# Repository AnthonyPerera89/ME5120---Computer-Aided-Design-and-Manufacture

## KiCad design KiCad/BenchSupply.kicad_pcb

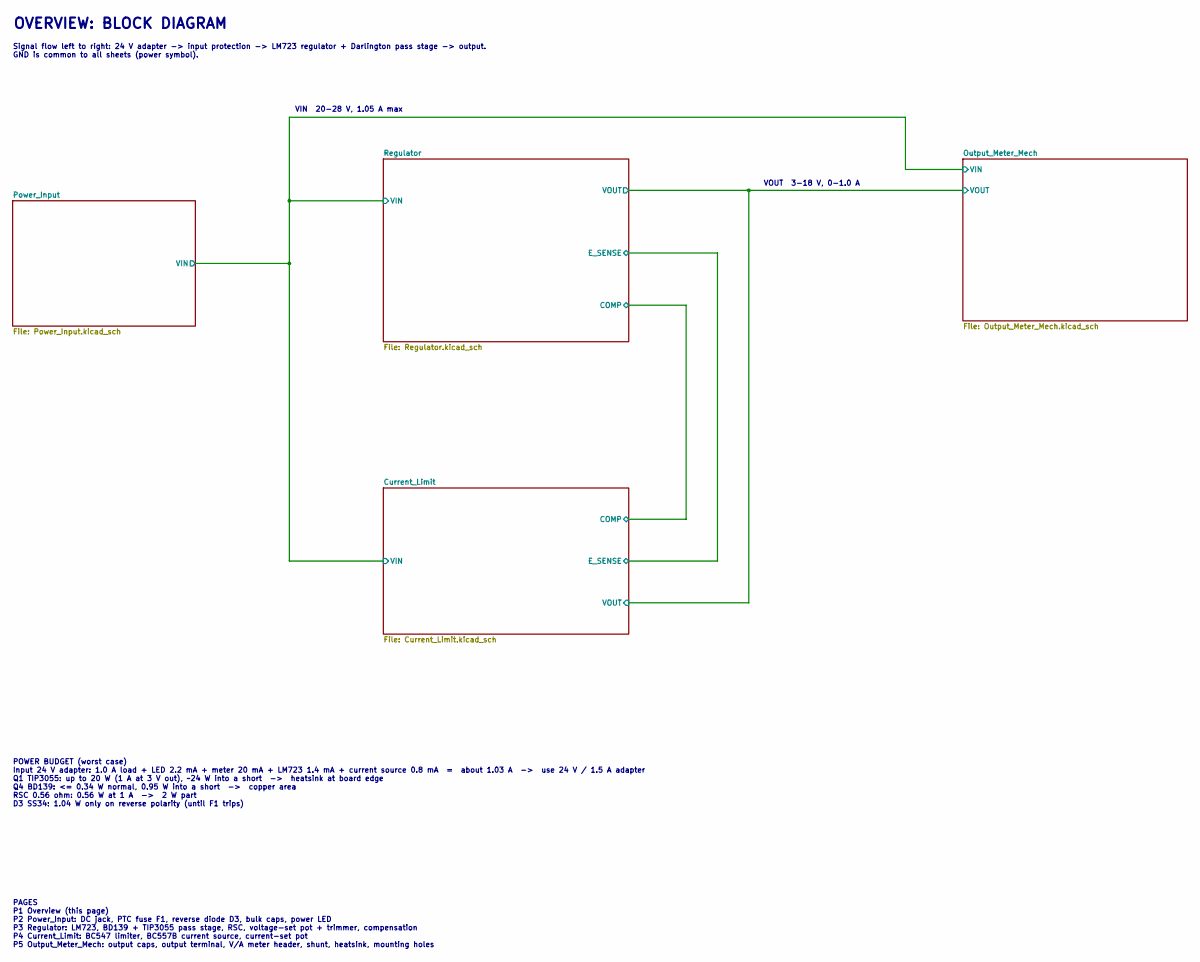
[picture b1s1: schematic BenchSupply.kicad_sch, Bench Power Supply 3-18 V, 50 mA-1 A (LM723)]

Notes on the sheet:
PAGES P1 Overview (this page) P2 Power_Input: DC jack, PTC fuse F1, reverse diode D3, bulk caps, power LED P3 Regulator: LM723, BD139 + TIP3055 pass stage, RSC, voltage-set pot + trimmer, compensation P4 Current_Limit: BC547 limiter, BC557B current source, current-set pot P5 Output_Meter_Mech: outp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
Signal flow left to right: 24 V adapter -> input protection -> LM723 regulator + Darlington pass stage -> output. GND is common to all sheets (power symbol).
VIN 20-28 V, 1.05 A max
OVERVIEW: BLOCK DIAGRAM
POWER BUDGET (worst case) Input 24 V adapter: 1.0 A load + LED 2.2 mA + meter 20 mA + LM723 1.4 mA + current source 0.8 mA = about 1.03 A -> use 24 V / 1.5 A adapter Q1 TIP3055: up to 20 W (1 A at 3 V out), ~24 W into a short -> heatsink at board edge Q4 BD139: <= 0.34 W normal, 0.95 W into a short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
VOUT 3-18 V, 0-1.0 A

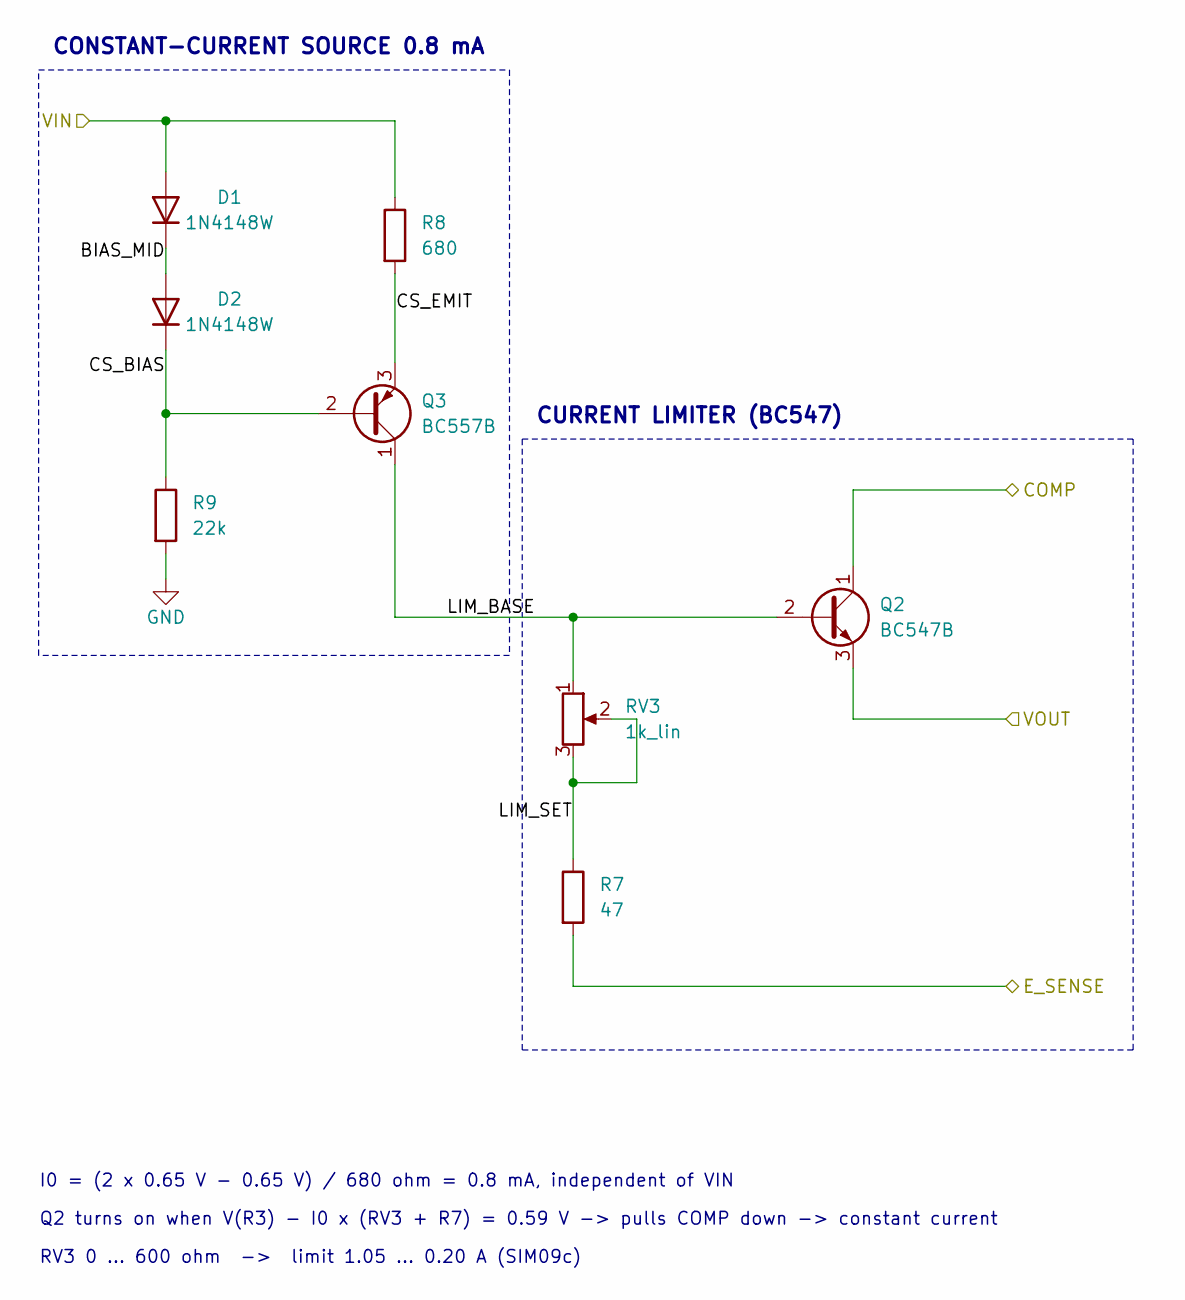
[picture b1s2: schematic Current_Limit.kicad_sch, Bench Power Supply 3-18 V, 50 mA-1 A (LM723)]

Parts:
D1, D2: 1N4148W; D_SOD-123; MPN Vishay 1N4148W
Q2: BC547B; TO-92_Inline_Wide; Rating Brief part; turns on at VBE ~0.59 V and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; MPN onsemi BC547BTA
Q3: BC557B; TO-92_Inline_Wide; Rating Constant-current source I0 = (2 VD - VE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; MPN onsemi BC557BTA
R7: 47; R_0805_2012Metric; MPN Yageo RC0805FR-0747RL
R8: 680; R_0805_2012Metric; MPN Yageo RC0805FR-07680RL
R9: 22k; R_0805_2012Metric; MPN Yageo RC0805FR-0722KL
RV3: 1k_lin; Potentiometer_Alps_RK163_Single_Horizontal; Rating PCB-mount shaft pot, linear; wired as r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; MPN Alps RK163 series 16 mm, M7 bushing, 1k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

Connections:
/Current_Limit/BIAS_MID: D1.1 (K), D2.2 (A)
/Current_Limit/COMP: Q2.1 (C); also elsewhere on the board
/Current_Limit/CS_BIAS: D2.1 (K), Q3.2 (B), R9.1
/Current_Limit/CS_EMIT: Q3.3 (E), R8.2
/Current_Limit/E_SENSE: R7.2; also elsewhere on the board
/Current_Limit/LIM_BASE: Q2.2 (B), Q3.1 (C), RV3.1
/Current_Limit/LIM_SET: R7.1, RV3.2, RV3.3
/Current_Limit/VIN: D1.2 (A), R8.1; also elsewhere on the board
/Regulator/VOUT: Q2.3 (E); also elsewhere on the board
GND: R9.2; also elsewhere on the board

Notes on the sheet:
I0 = (2 x 0.65 V - 0.65 V) / 680 ohm = 0.8 mA, independent of VIN
RV3 0 ... 600 ohm -> limit 1.05 ... 0.20 A (SIM09c)
CONSTANT-CURRENT SOURCE 0.8 mA
CURRENT LIMITER (BC547)
Q2 turns on when V(R3) - I0 x (RV3 + R7) = 0.59 V -> pulls COMP down -> constant current

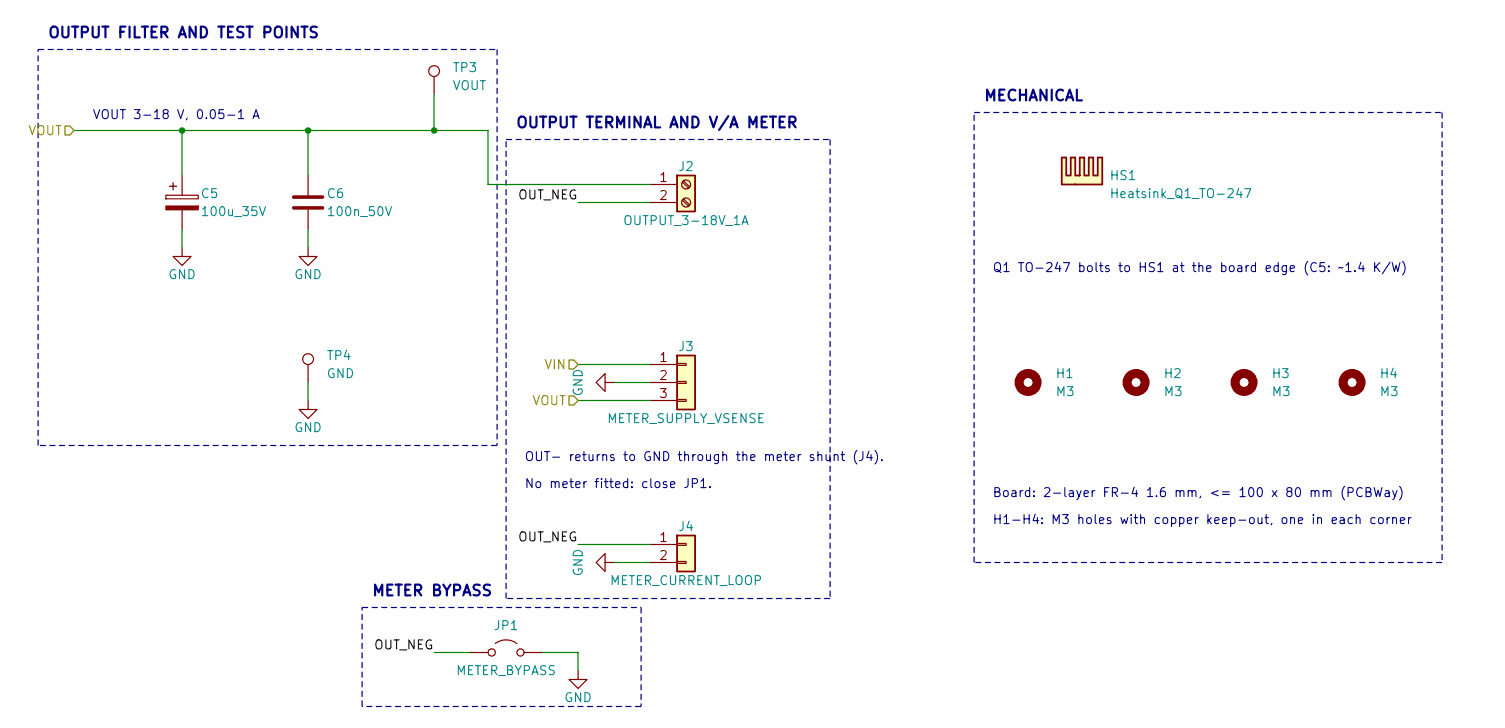
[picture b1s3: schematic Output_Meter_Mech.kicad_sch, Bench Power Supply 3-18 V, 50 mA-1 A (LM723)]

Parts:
C5: 100u_35V; CP_Radial_D6.3mm_P2.50mm; MPN Panasonic EEU-FR1V101 (100uF 35V 6.3x11)
C6: 100n_50V; C_0805_2012Metric; MPN Samsung CL21B104KBCNNNC
H1, H2, H3, H4: M3; MountingHole_3.2mm_M3
HS1: Heatsink_Q1_TO-247; Heatsink_AAVID_Extruded_531302B02500G_34.9x12.7mm_H63.5mm; Rating Board-mount TO-247 extrusion 34.9x12.7x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; MPN Aavid (Boyd) 531302B02500G
J2: OUTPUT_3-18V_1A; TerminalBlock_Phoenix_MKDS-1,5-2-5.08_1x02_P5.08mm_Horizont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; MPN Phoenix Contact 1715721 (MKDS 1,5/2-5,0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
J3: METER_SUPPLY_VSENSE; PinHeader_1x03_P2.54mm_Vertical; Rating V/A meter thin lead: 1 = VIN supply (~2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; MPN 2.54 mm male header 1x3
J4: METER_CURRENT_LOOP; TerminalBlock_Phoenix_MKDS-1,5-2-5.08_1x02_P5.08mm_Horizont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; Rating V/A meter thick leads (1 A): 1 = OUT- f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; MPN Phoenix Contact 1715721 (MKDS 1,5/2-5,0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
JP1: METER_BYPASS; PinHeader_1x02_P2.54mm_Vertical; Rating Close (solder bridge / 2-pin link) when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; MPN 2.54 mm male header 1x2 + shunt
TP3: VOUT; TestPoint_THTPad_D2.0mm_Drill1.0mm
TP4: GND; TestPoint_THTPad_D2.0mm_Drill1.0mm

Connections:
/Current_Limit/VIN: J3.1; also elsewhere on the board
/Output_Meter_Mech/OUT_NEG: J2.2, J4.1, JP1.1 (A)
/Regulator/VOUT: C5.1, C6.1, J2.1, J3.3, TP3.1 (1_1); also elsewhere on the board
GND: C5.2, C6.2, J3.2, J4.2, JP1.2 (B), TP4.1 (1_1); also elsewhere on the board

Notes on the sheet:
OUTPUT FILTER AND TEST POINTS
No meter fitted: close JP1.
Q1 TO-247 bolts to HS1 at the board edge (C5: ~1.4 K/W)
METER BYPASS
H1-H4: M3 holes with copper keep-out, one in each corner
OUTPUT TERMINAL AND V/A METER
VOUT 3-18 V, 0.05-1 A
MECHANICAL
Board: 2-layer FR-4 1.6 mm, <= 100 x 80 mm (PCBWay)
OUT- returns to GND through the meter shunt (J4).

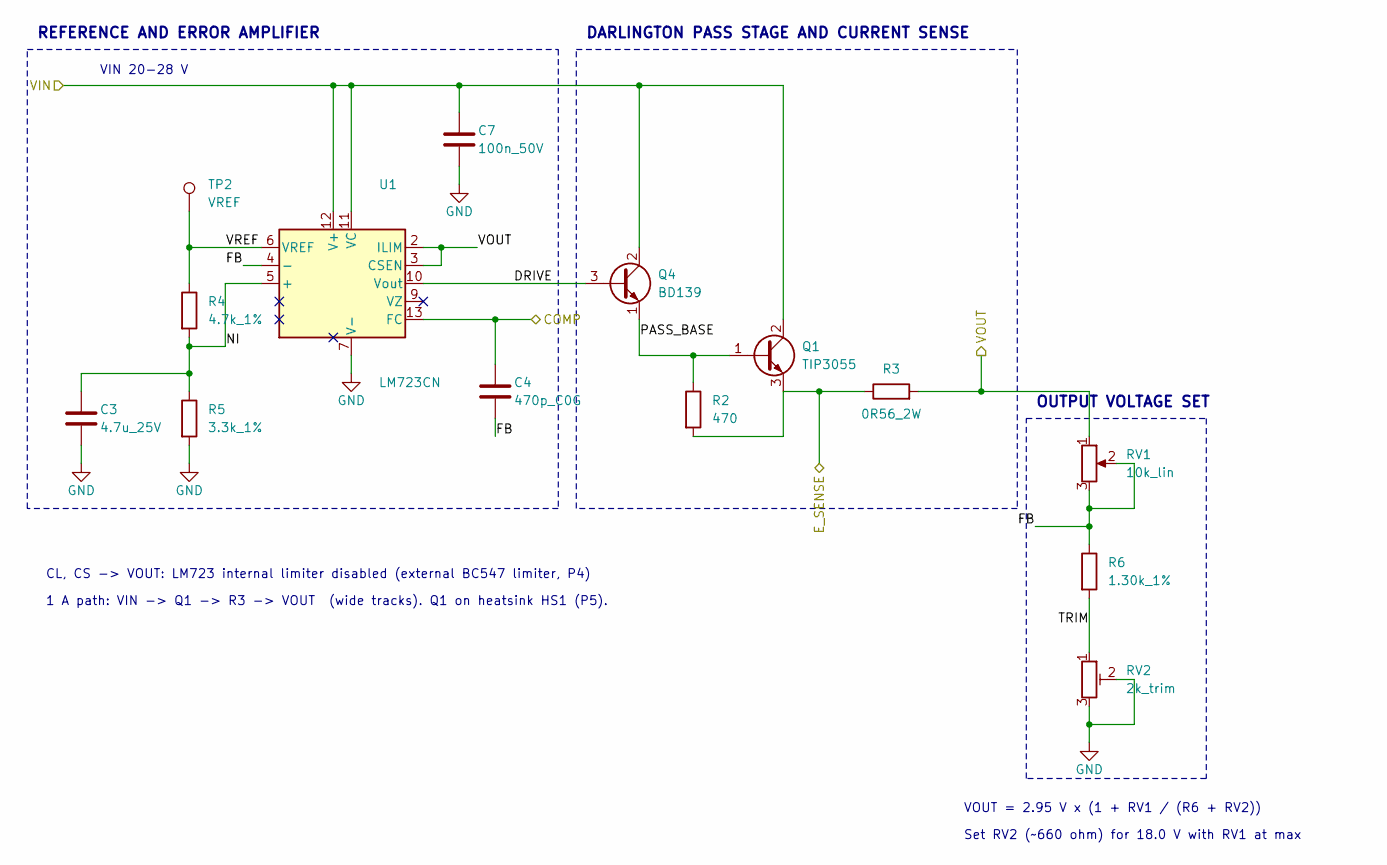
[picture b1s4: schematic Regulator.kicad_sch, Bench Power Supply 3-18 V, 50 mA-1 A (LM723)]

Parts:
C3: 4.7u_25V; C_1206_3216Metric; MPN Samsung CL31B475KAHNNNE
C4: 470p_C0G; C_0805_2012Metric; MPN Murata GRM2165C1H471JA01D
C7: 100n_50V; C_0805_2012Metric; Rating Decoupling at U1 V+/VC pins (place with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; MPN Samsung CL21B104KBCNNNC
Q1: TIP3055; TO-247-3_Vertical; Rating TO-247 on board-edge heatsink; 20 W at 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; MPN onsemi TIP3055G
Q4: BD139; TO-126-3_Vertical; Rating TO-126 driver; 0.34 W normal, 0.95 W in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; MPN onsemi BD139G
R2: 470; R_0805_2012Metric; MPN Yageo RC0805FR-07470RL
R3: 0R56_2W; R_Axial_DIN0414_L11.9mm_D4.5mm_P15.24mm_Horizontal; Rating 0.56 ohm 2 W axial (0.62 W at 1.05 A); 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; MPN Vishay PR02 series 0.56 ohm 2 W axial
R4: 4.7k_1%; R_0805_2012Metric; MPN Yageo RC0805FR-074K7L
R5: 3.3k_1%; R_0805_2012Metric; MPN Yageo RC0805FR-073K3L
R6: 1.30k_1%; R_0805_2012Metric; MPN Yageo RC0805FR-071K3L
RV1: 10k_lin; Potentiometer_Alps_RK163_Single_Horizontal; Rating PCB-mount shaft pot, linear; wired as r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; MPN Alps RK163 series 16 mm, M7 bushing, 10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
RV2: 2k_trim; Potentiometer_Bourns_3296W_Vertical; Rating Multi-turn trimmer, rheostat; set ~660 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; MPN Bourns 3296W-1-202LF
TP2: VREF; TestPoint_THTPad_D2.0mm_Drill1.0mm
U1: LM723CN; DIP-14_W7.62mm; MPN TI LM723CN

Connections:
/Current_Limit/COMP: C4.1, U1.13 (FC); also elsewhere on the board
/Current_Limit/E_SENSE: Q1.3 (E), R2.2, R3.1; also elsewhere on the board
/Current_Limit/VIN: C7.1, Q1.2 (C), Q4.2 (C), U1.11 (VC), U1.12 (V+); also elsewhere on the board
/Regulator/DRIVE: Q4.3 (B), U1.10 (Vout)
/Regulator/FB: C4.2, R6.1, RV1.2, RV1.3, U1.4 (-)
/Regulator/NI: C3.1, R4.2, R5.1, U1.5 (+)
/Regulator/PASS_BASE: Q1.1 (B), Q4.1 (E), R2.1
/Regulator/TRIM: R6.2, RV2.1
/Regulator/VOUT: R3.2, RV1.1, U1.2 (ILIM), U1.3 (CSEN); also elsewhere on the board
/Regulator/VREF: R4.1, TP2.1 (1_1), U1.6 (VREF)
GND: C3.2, C7.2, R5.2, RV2.2, RV2.3, U1.7 (V-); also elsewhere on the board

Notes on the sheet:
VOUT = 2.95 V x (1 + RV1 / (R6 + RV2))
DARLINGTON PASS STAGE AND CURRENT SENSE
REFERENCE AND ERROR AMPLIFIER
OUTPUT VOLTAGE SET
Set RV2 (~660 ohm) for 18.0 V with RV1 at max
1 A path: VIN -> Q1 -> R3 -> VOUT (wide tracks). Q1 on heatsink HS1 (P5).
CL, CS -> VOUT: LM723 internal limiter disabled (external BC547 limiter, P4)
VIN 20-28 V

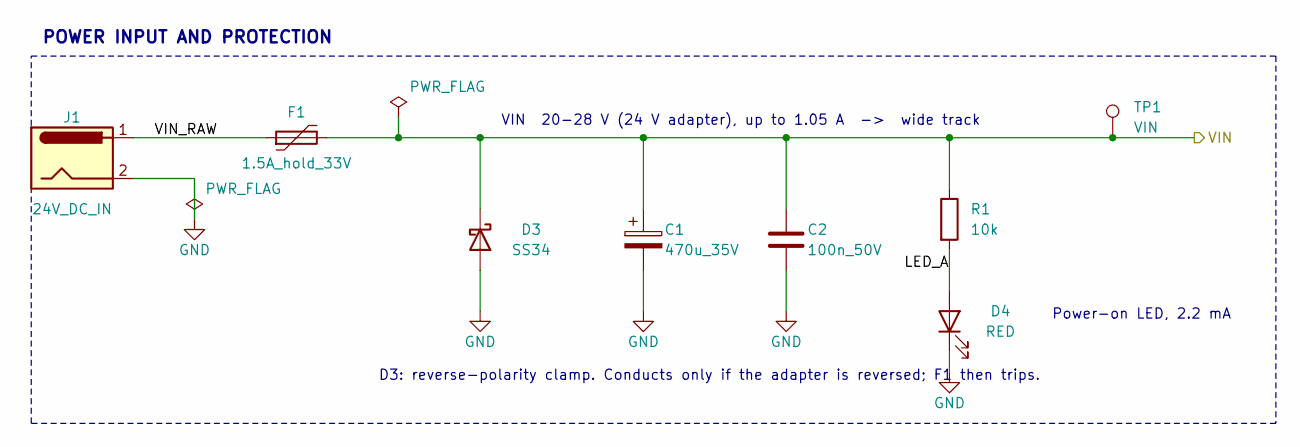
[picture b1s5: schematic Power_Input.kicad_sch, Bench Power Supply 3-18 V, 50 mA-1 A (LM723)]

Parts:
C1: 470u_35V; CP_Radial_D10.0mm_P5.00mm; Rating 35 V, low-ESR electrolytic; MPN 470uF 35V 10x16 low-ESR
C2: 100n_50V; C_0805_2012Metric; MPN Samsung CL21B104KBCNNNC
D3: SS34; D_SMA; Rating 3 A, 40 V Schottky, reverse-polarity cl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; MPN SS34 (onsemi/Vishay)
D4: RED; LED_0805_2012Metric; Rating Power-on LED, 2.2 mA via R1; MPN Lite-On LTST-C171KRKT
F1: 1.5A_hold_33V; Fuse_2920_7451Metric; Rating PTC 2920 SMD: 1.5 A hold, 3 A trip, 33 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; MPN Bourns MF-SM150/33-2
J1: 24V_DC_IN; BarrelJack_CUI_PJ-063AH_Horizontal; Rating 5.5/2.1 mm, 2.5 A; centre pin +24 V; MPN CUI PJ-063AH
R1: 10k; R_0805_2012Metric; MPN Yageo RC0805FR-0710KL
TP1: VIN; TestPoint_THTPad_D2.0mm_Drill1.0mm

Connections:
/Current_Limit/VIN: C1.1, C2.1, D3.1 (K), F1.2, R1.1, TP1.1 (1_1); also elsewhere on the board
/Power_Input/LED_A: D4.2 (A), R1.2
/Power_Input/VIN_RAW: F1.1, J1.1
GND: C1.2, C2.2, D3.2 (A), D4.1 (K), J1.2; also elsewhere on the board

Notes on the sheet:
POWER INPUT AND PROTECTION
VIN 20-28 V (24 V adapter), up to 1.05 A -> wide track
D3: reverse-polarity clamp. Conducts only if the adapter is reversed; F1 then trips.
Power-on LED, 2.2 mA

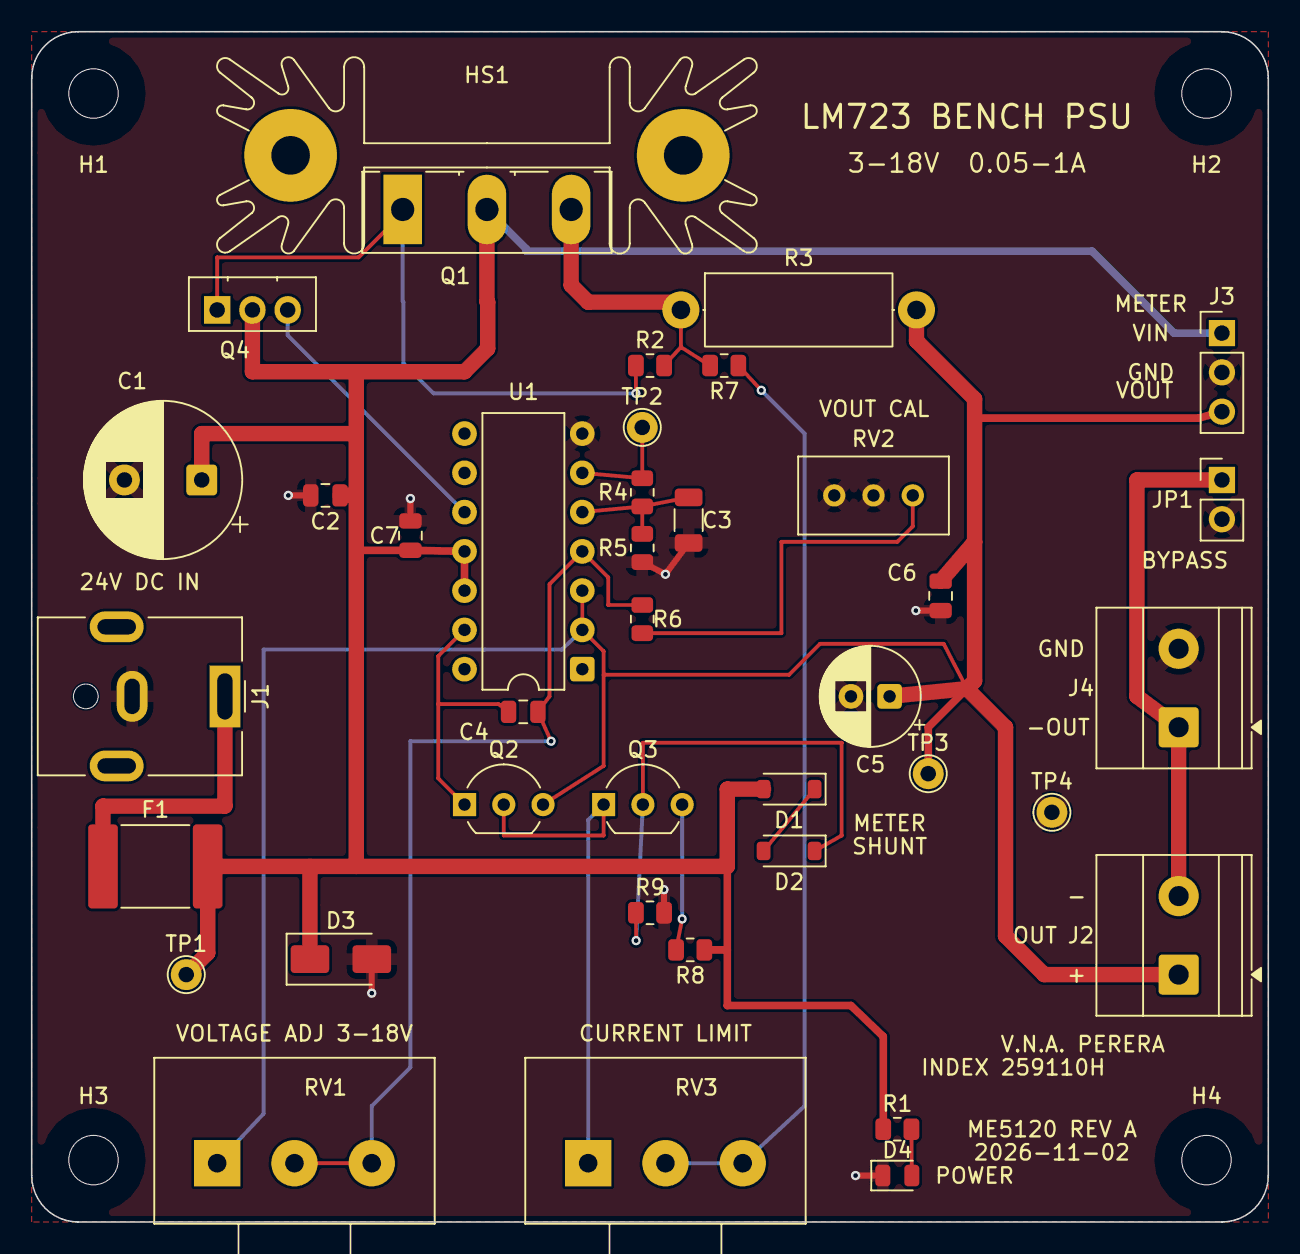
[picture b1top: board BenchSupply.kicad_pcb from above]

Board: 2 copper layers, 80.0 x 77.0 mm, 43 parts (0 on the bottom side), 19 nets.

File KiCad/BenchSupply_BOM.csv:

Ref,Value,Footprint,MPN / part,Rating / note,Page,Mount
C1,470u_35V,Capacitor_THT:CP_Radial_D10.0mm_P5.00mm,470uF 35V 10x16 low-ESR,"35 V, low-ESR electrolytic",P2,THT
C2,100n_50V,Capacitor_SMD:C_0805_2012Metric,Samsung CL21B104KBCNNNC,,P2,SMD
C3,4.7u_25V,Capacitor_SMD:C_1206_3216Metric,Samsung CL31B475KAHNNNE,,P3,SMD
C4,470p_C0G,Capacitor_SMD:C_0805_2012Metric,Murata GRM2165C1H471JA01D,,P3,SMD
C5,100u_35V,Capacitor_THT:CP_Radial_D6.3mm_P2.50mm,Panasonic EEU-FR1V101 (100uF 35V 6.3x11),,P5,THT
C6,100n_50V,Capacitor_SMD:C_0805_2012Metric,Samsung CL21B104KBCNNNC,,P5,SMD
C7,100n_50V,Capacitor_SMD:C_0805_2012Metric,Samsung CL21B104KBCNNNC,Decoupling at U1 V+/VC pins (place within 5 mm),P3,SMD
D1,1N4148W,Diode_SMD:D_SOD-123,Vishay 1N4148W,,P4,SMD
D2,1N4148W,Diode_SMD:D_SOD-123,Vishay 1N4148W,,P4,SMD
D3,SS34,Diode_SMD:D_SMA,SS34 (onsemi/Vishay),"3 A, 40 V Schottky, reverse-polarity clamp",P2,SMD
D4,RED,LED_SMD:LED_0805_2012Metric,Lite-On LTST-C171KRKT,"Power-on LED, 2.2 mA via R1",P2,SMD
F1,1.5A_hold_33V,Fuse:Fuse_2920_7451Metric,Bourns MF-SM150/33-2,"PTC 2920 SMD: 1.5 A hold, 3 A trip, 33 V (D25)",P2,SMD
HS1,Heatsink_Q1_TO-247,,"TO-247 heatsink ~1.4 K/W (off-board, edge overhang)","Board-edge heatsink for Q1, ~1.4 K/W (C5 to be rechecked for 25 W short)",P5,off-board
J1,24V_DC_IN,Connector_BarrelJack:BarrelJack_CUI_PJ-102AH_Horizontal,CUI PJ-102AH,"5.5/2.1 mm, 2.5 A; centre pin +24 V",P2,THT
J2,OUTPUT_3-18V_1A,"TerminalBlock_Phoenix:TerminalBlock_Phoenix_MKDS-1,5-2-5.08_1x02_P5.08mm_Horizontal","Phoenix Contact 1715721 (MKDS 1,5/2-5,08)",,P5,THT
J3,METER_SUPPLY_VSENSE,Connector_PinHeader_2.54mm:PinHeader_1x03_P2.54mm_Vertical,2.54 mm male header 1x3,"V/A meter thin lead: 1 = VIN supply (~20 mA), 2 = GND, 3 = VOUT sense",P5,THT
J4,METER_CURRENT_LOOP,"TerminalBlock_Phoenix:TerminalBlock_Phoenix_MKDS-1,5-2-5.08_1x02_P5.08mm_Horizontal","Phoenix Contact 1715721 (MKDS 1,5/2-5,08)","V/A meter thick leads (1 A): 1 = OUT- from J2, 2 = GND; module shunt in series",P5,THT
JP1,METER_BYPASS,Connector_PinHeader_2.54mm:PinHeader_1x02_P2.54mm_Vertical,2.54 mm male header 1x2 + shunt,"Close (solder bridge / 2-pin link) when no meter is fitted: OUT- to GND, 1 A",P5,THT
Q1,TIP3055,Package_TO_SOT_THT:TO-247-3_Vertical,onsemi TIP3055G,"TO-247 on board-edge heatsink; 20 W at 1 A / 3 V, ~24 W into a short",P3,THT
Q2,BC547B,Package_TO_SOT_THT:TO-92_Inline,onsemi BC547BTA,Brief part; turns on at VBE ~0.59 V and pulls U1 COMP down,P4,THT
Q3,BC557B,Package_TO_SOT_THT:TO-92_Inline,onsemi BC557BTA,Constant-current source I0 = (2 VD - VEB)/R8 = 0.8 mA,P4,THT
Q4,BD139,Package_TO_SOT_THT:TO-126-3_Vertical,onsemi BD139G,"TO-126 driver; 0.34 W normal, 0.95 W into a short (copper area)",P3,THT
R1,10k,Resistor_SMD:R_0805_2012Metric,Yageo RC0805FR-0710KL,,P2,SMD
R2,470,Resistor_SMD:R_0805_2012Metric,Yageo RC0805FR-07470RL,,P3,SMD
R3,0R56_2W,Resistor_THT:R_Axial_DIN0414_L11.9mm_D4.5mm_P15.24mm_Horizontal,Vishay PR02 series 0.56 ohm 2 W axial,0.56 ohm 2 W axial (0.62 W at 1.05 A); current-sense resistor RSC,P3,THT
R4,4.7k_1%,Resistor_SMD:R_0805_2012Metric,Yageo RC0805FR-074K7L,,P3,SMD
R5,3.3k_1%,Resistor_SMD:R_0805_2012Metric,Yageo RC0805FR-073K3L,,P3,SMD
R6,1.30k_1%,Resistor_SMD:R_0805_2012Metric,Yageo RC0805FR-071K3L,,P3,SMD
R7,47,Resistor_SMD:R_0805_2012Metric,Yageo RC0805FR-0747RL,,P4,SMD
R8,680,Resistor_SMD:R_0805_2012Metric,Yageo RC0805FR-07680RL,,P4,SMD
R9,22k,Resistor_SMD:R_0805_2012Metric,Yageo RC0805FR-0722KL,,P4,SMD
RV1,10k_lin,Potentiometer_THT:Potentiometer_Alps_RK09K_Single_Vertical,Alps RK09K1130A 10k lin,"PCB-mount shaft pot, linear; wired as rheostat (voltage set 3-18 V)",P3,THT
RV2,2k_trim,Potentiometer_THT:Potentiometer_Bourns_3296W_Vertical,Bourns 3296W-1-202LF,"Multi-turn trimmer, rheostat; set ~660 ohm so max output = 18.0 V",P3,THT
RV3,1k_lin,Potentiometer_THT:Potentiometer_Alps_RK09K_Single_Vertical,Alps RK09K1130A 1k lin,"PCB-mount shaft pot, linear; wired as rheostat (current limit 50 mA-1.05 A)",P4,THT
U1,LM723CN,Package_DIP:DIP-14_W7.62mm,TI LM723CN,,P3,THT
